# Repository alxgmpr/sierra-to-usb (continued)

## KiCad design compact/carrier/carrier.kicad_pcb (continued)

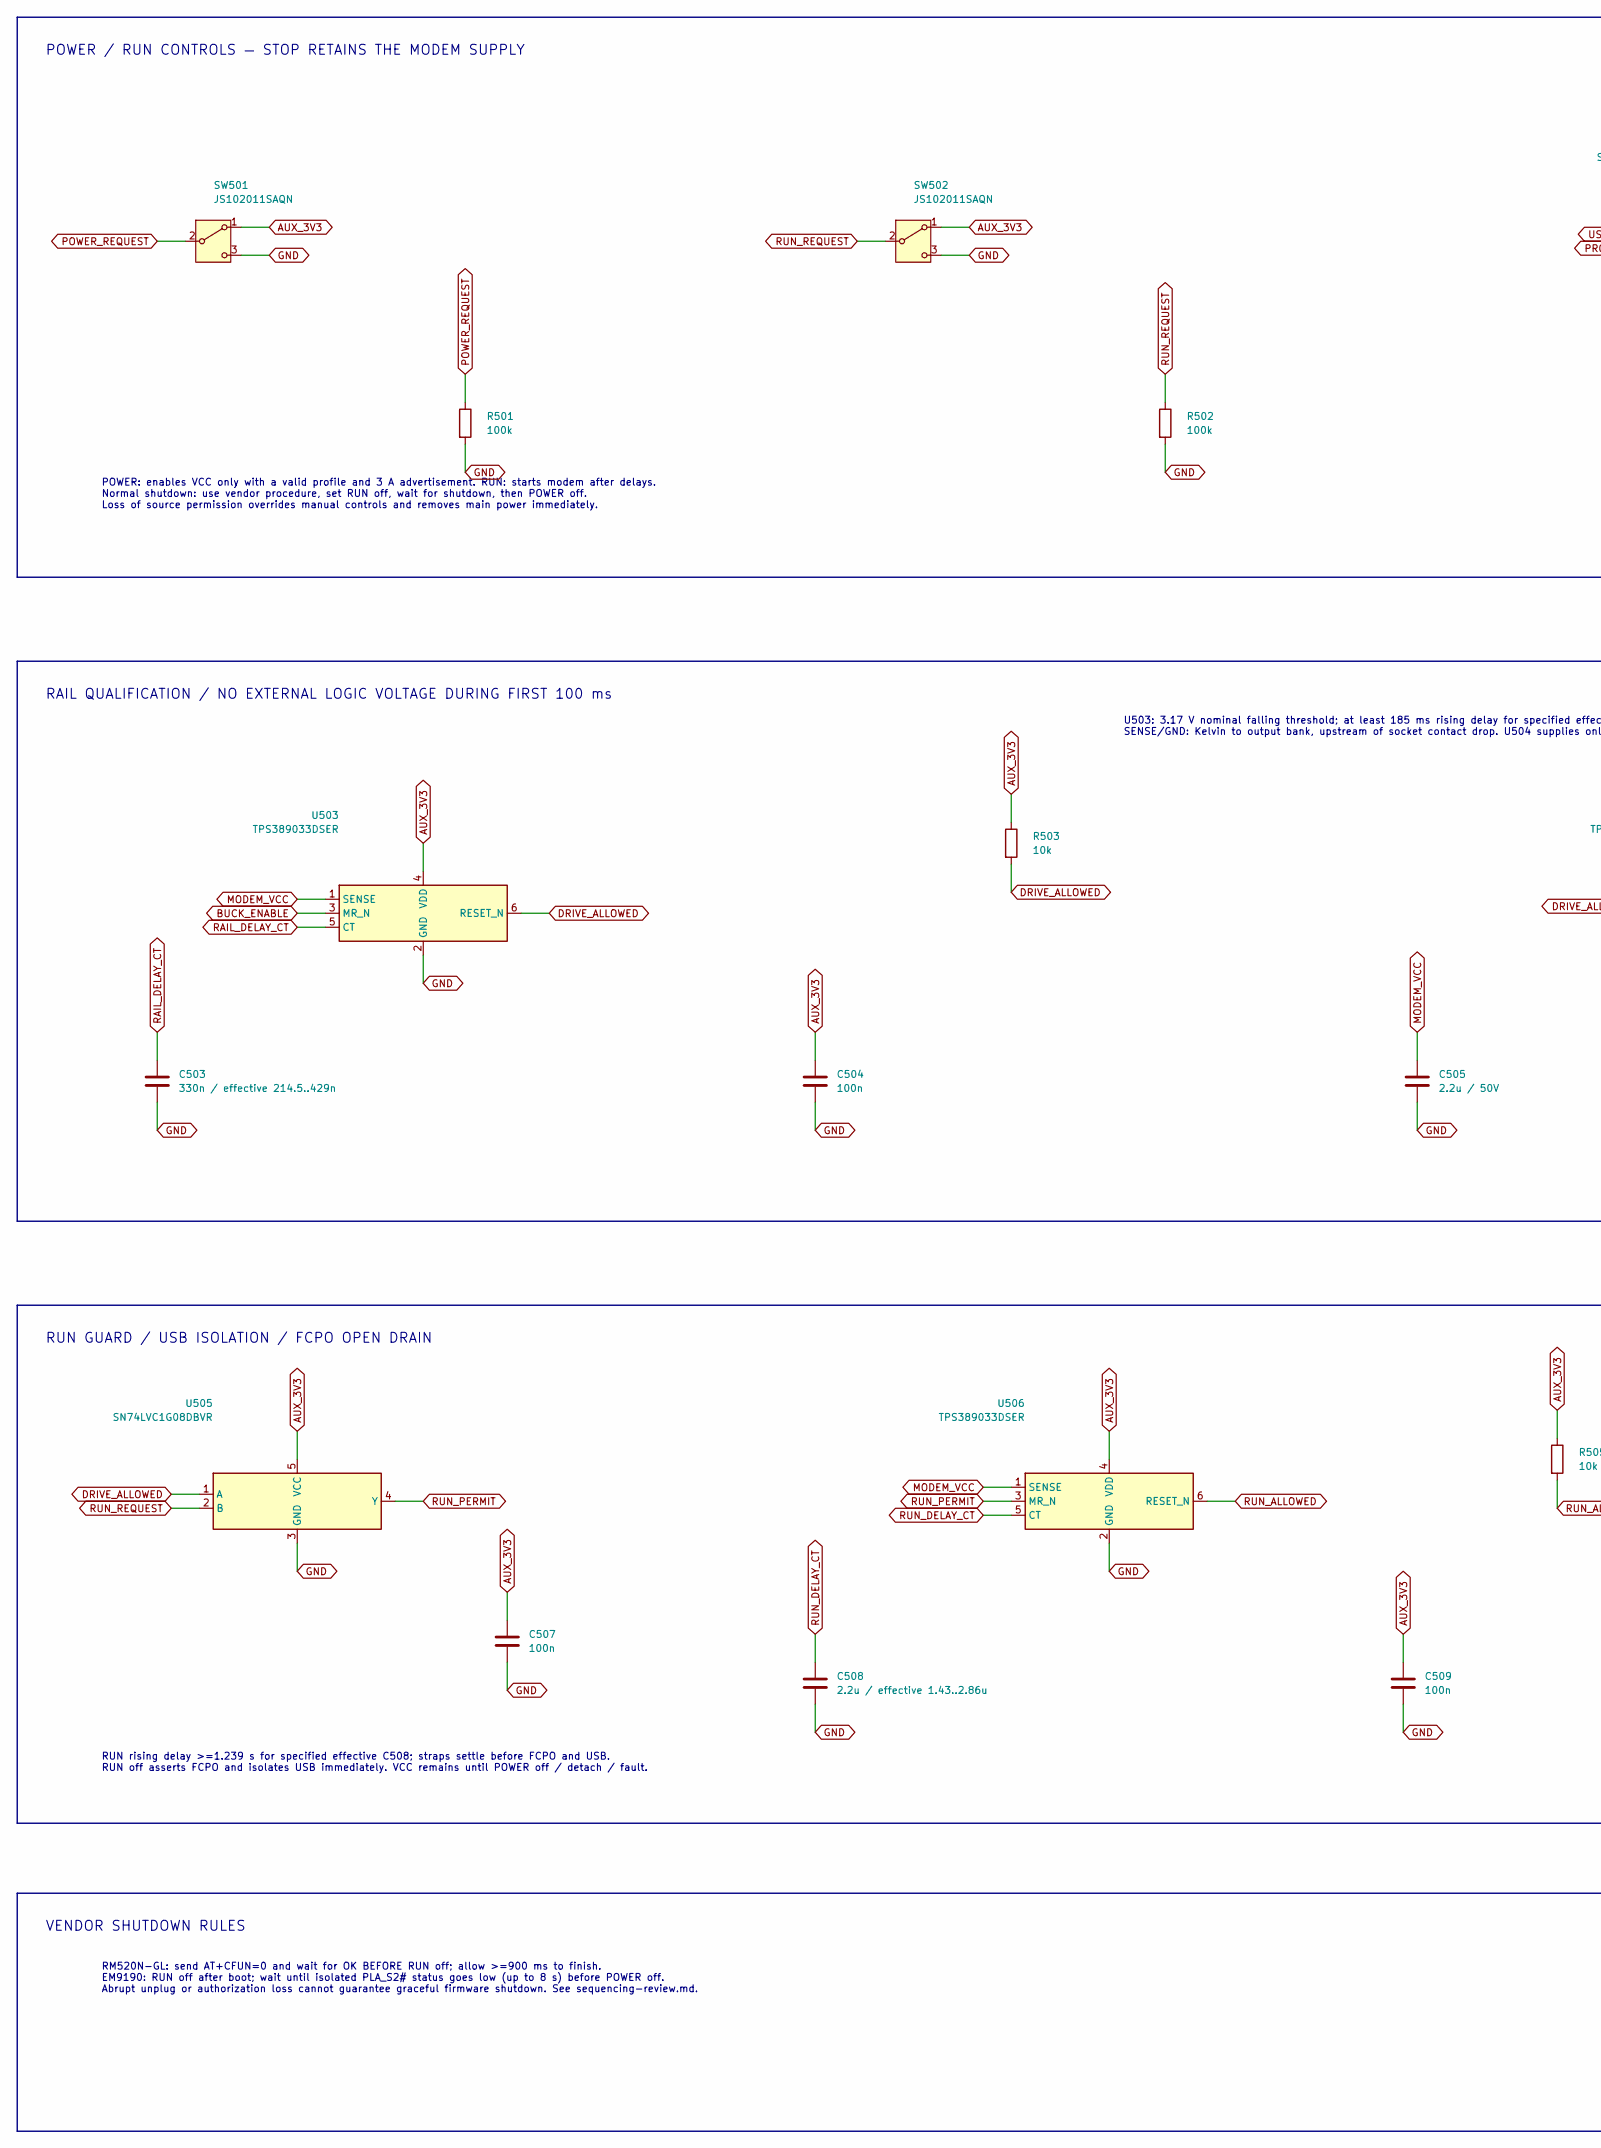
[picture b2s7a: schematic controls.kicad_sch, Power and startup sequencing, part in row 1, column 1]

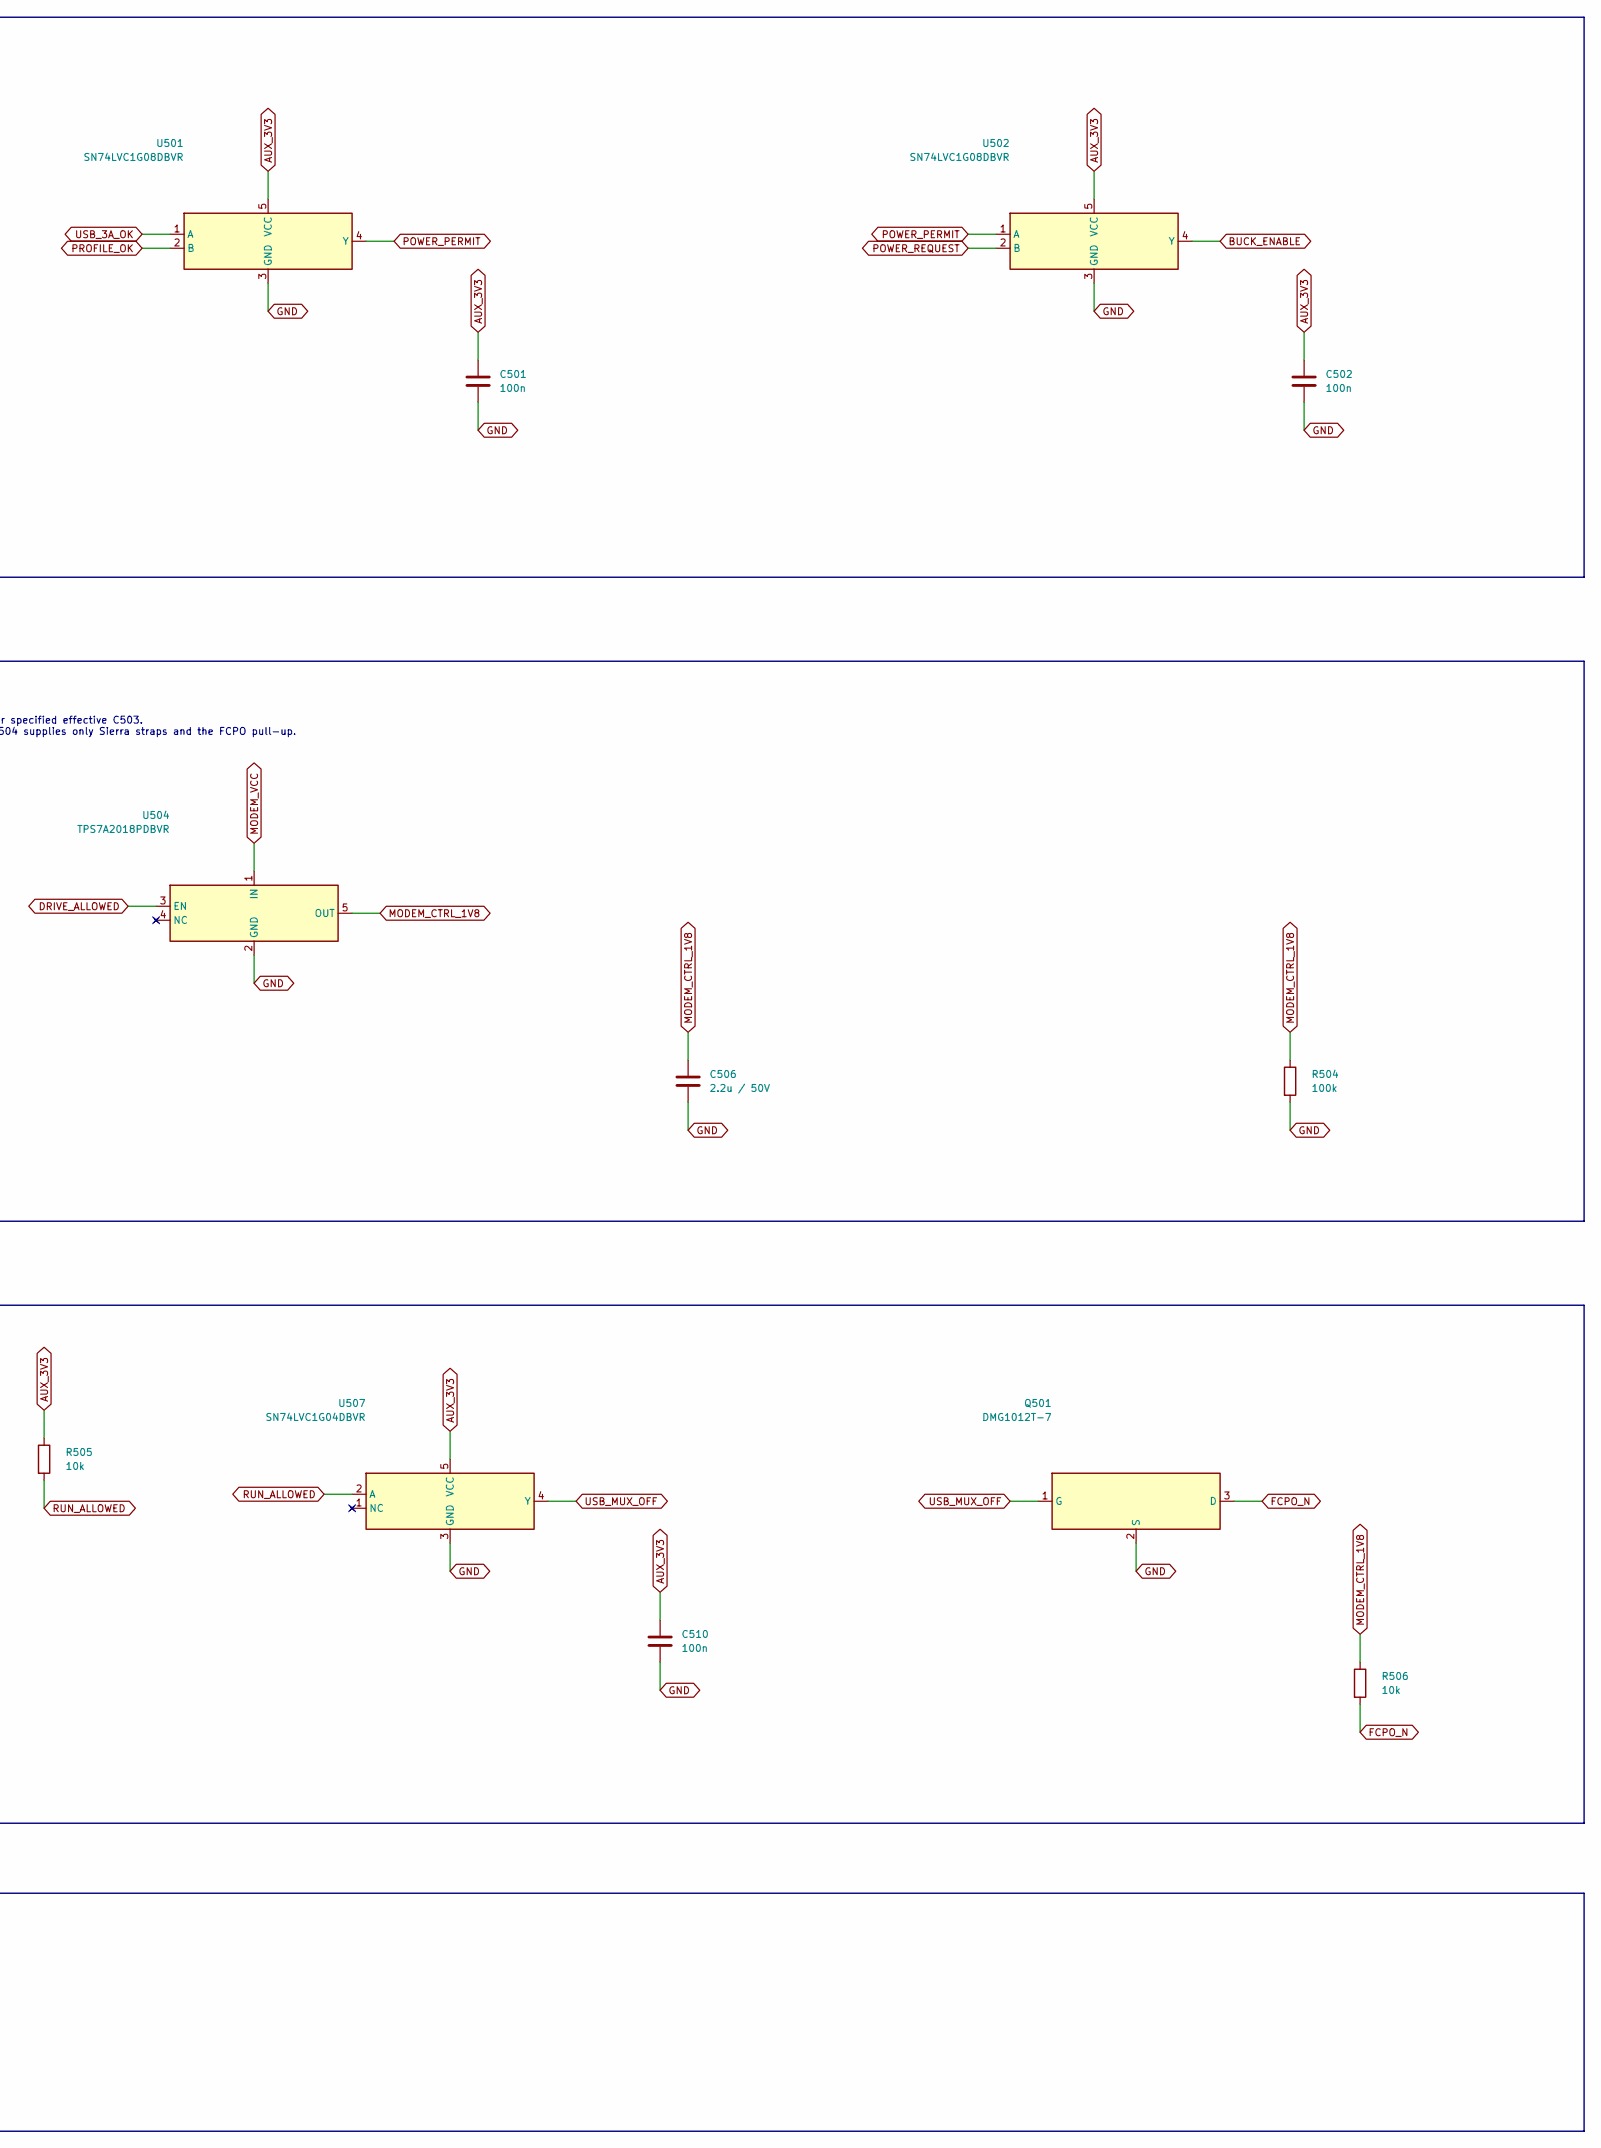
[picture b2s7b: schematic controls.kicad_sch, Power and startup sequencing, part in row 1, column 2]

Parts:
C501, C502, C504, C507, C509, C510: 100n; C_0805_2012Metric; MPN C2012X7R1H104K085AA
C503: 330n / effective 214.5..429n; C_0805_2012Metric; MPN C2012X7R1H334K125AA
C505, C506: 2.2u / 50V; C_1206_3216Metric; MPN C3216X7R1H225K160AB
C508: 2.2u / effective 1.43..2.86u; C_1206_3216Metric; MPN C3216X7R1H225K160AB
Q501: DMG1012T-7; SOT-523; MPN DMG1012T-7
R501, R502, R504: 100k; R_0603_1608Metric; MPN RC0603FR-07100KL
R503, R505, R506: 10k; R_0603_1608Metric; MPN RC0603FR-0710KL
SW501, SW502: JS102011SAQN; SW_SPDT_CK_JS102011SAQN; MPN JS102011SAQN
U501, U502, U505: SN74LVC1G08DBVR; SOT-23-5; MPN SN74LVC1G08DBVR
U503, U506: TPS389033DSER; WSON-6_1.5x1.5mm_P0.5mm; MPN TPS389033DSER
U504: TPS7A2018PDBVR; SOT-23-5; MPN TPS7A2018PDBVR
U507: SN74LVC1G04DBVR; SOT-23-5; MPN SN74LVC1G04DBVR

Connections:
AUX_3V3: C501.1, C502.1, C504.1, C507.1, C509.1, C510.1, R503.1, R505.1, SW501.1 (A), SW502.1 (A), U501.5 (VCC), U502.5 (VCC), U503.4 (VDD), U505.5 (VCC), U506.4 (VDD), U507.5 (VCC); also elsewhere on the board
BUCK_ENABLE: U502.4 (Y), U503.3 (MR_N); also elsewhere on the board
DRIVE_ALLOWED: R503.2, U503.6 (RESET_N), U504.3 (EN), U505.1 (A); also elsewhere on the board
FCPO_N: Q501.3 (D), R506.2; also elsewhere on the board
GND: C501.2, C502.2, C503.2, C504.2, C505.2, C506.2, C507.2, C508.2, C509.2, C510.2, Q501.2 (S), R501.2, R502.2, R504.2, SW501.3 (C), SW502.3 (C), U501.3 (GND), U502.3 (GND), U503.2 (GND), U504.2 (GND), U505.3 (GND), U506.2 (GND), U507.3 (GND); also elsewhere on the board
MODEM_CTRL_1V8: C506.1, R504.1, R506.1, U504.5 (OUT); also elsewhere on the board
MODEM_VCC: C505.1, U503.1 (SENSE), U504.1 (IN), U506.1 (SENSE); also elsewhere on the board
POWER_PERMIT: U501.4 (Y), U502.1 (A)
POWER_REQUEST: R501.1, SW501.2 (B), U502.2 (B)
PROFILE_OK: U501.2 (B); also elsewhere on the board
RAIL_DELAY_CT: C503.1, U503.5 (CT)
RUN_ALLOWED: R505.2, U506.6 (RESET_N), U507.2 (A); also elsewhere on the board
RUN_DELAY_CT: C508.1, U506.5 (CT)
RUN_PERMIT: U505.4 (Y), U506.3 (MR_N)
RUN_REQUEST: R502.1, SW502.2 (B), U505.2 (B)
USB_3A_OK: U501.1 (A); also elsewhere on the board
USB_MUX_OFF: Q501.1 (G), U507.4 (Y); also elsewhere on the board

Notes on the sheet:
POWER / RUN CONTROLS — STOP RETAINS THE MODEM SUPPLY
POWER: enables VCC only with a valid profile and 3 A advertisement. RUN: starts modem after delays. Normal shutdown: use vendor procedure, set RUN off, wait for shutdown, then POWER off. Loss of source permission overrides manual controls and removes main power immediately.
RAIL QUALIFICATION / NO EXTERNAL LOGIC VOLTAGE DURING FIRST 100 ms
U503: 3.17 V nominal falling threshold; at least 185 ms rising delay for specified effective C503. SENSE/GND: Kelvin to output bank, upstream of socket contact drop. U504 supplies only Sierra straps and the FCPO pull-up.
RUN GUARD / USB ISOLATION / FCPO OPEN DRAIN
RUN rising delay >=1.239 s for specified effective C508; straps settle before FCPO and USB. RUN off asserts FCPO and isolates USB immediately. VCC remains until POWER off / detach / fault.
VENDOR SHUTDOWN RULES
RM520N-GL: send AT+CFUN=0 and wait for OK BEFORE RUN off; allow >=900 ms to finish. EM9190: RUN off after boot; wait until isolated PLA_S2# status goes low (up to 8 s) before POWER off. Abrupt unplug or authorization loss cannot guarantee graceful firmware shutdown. See sequencing-review.md.

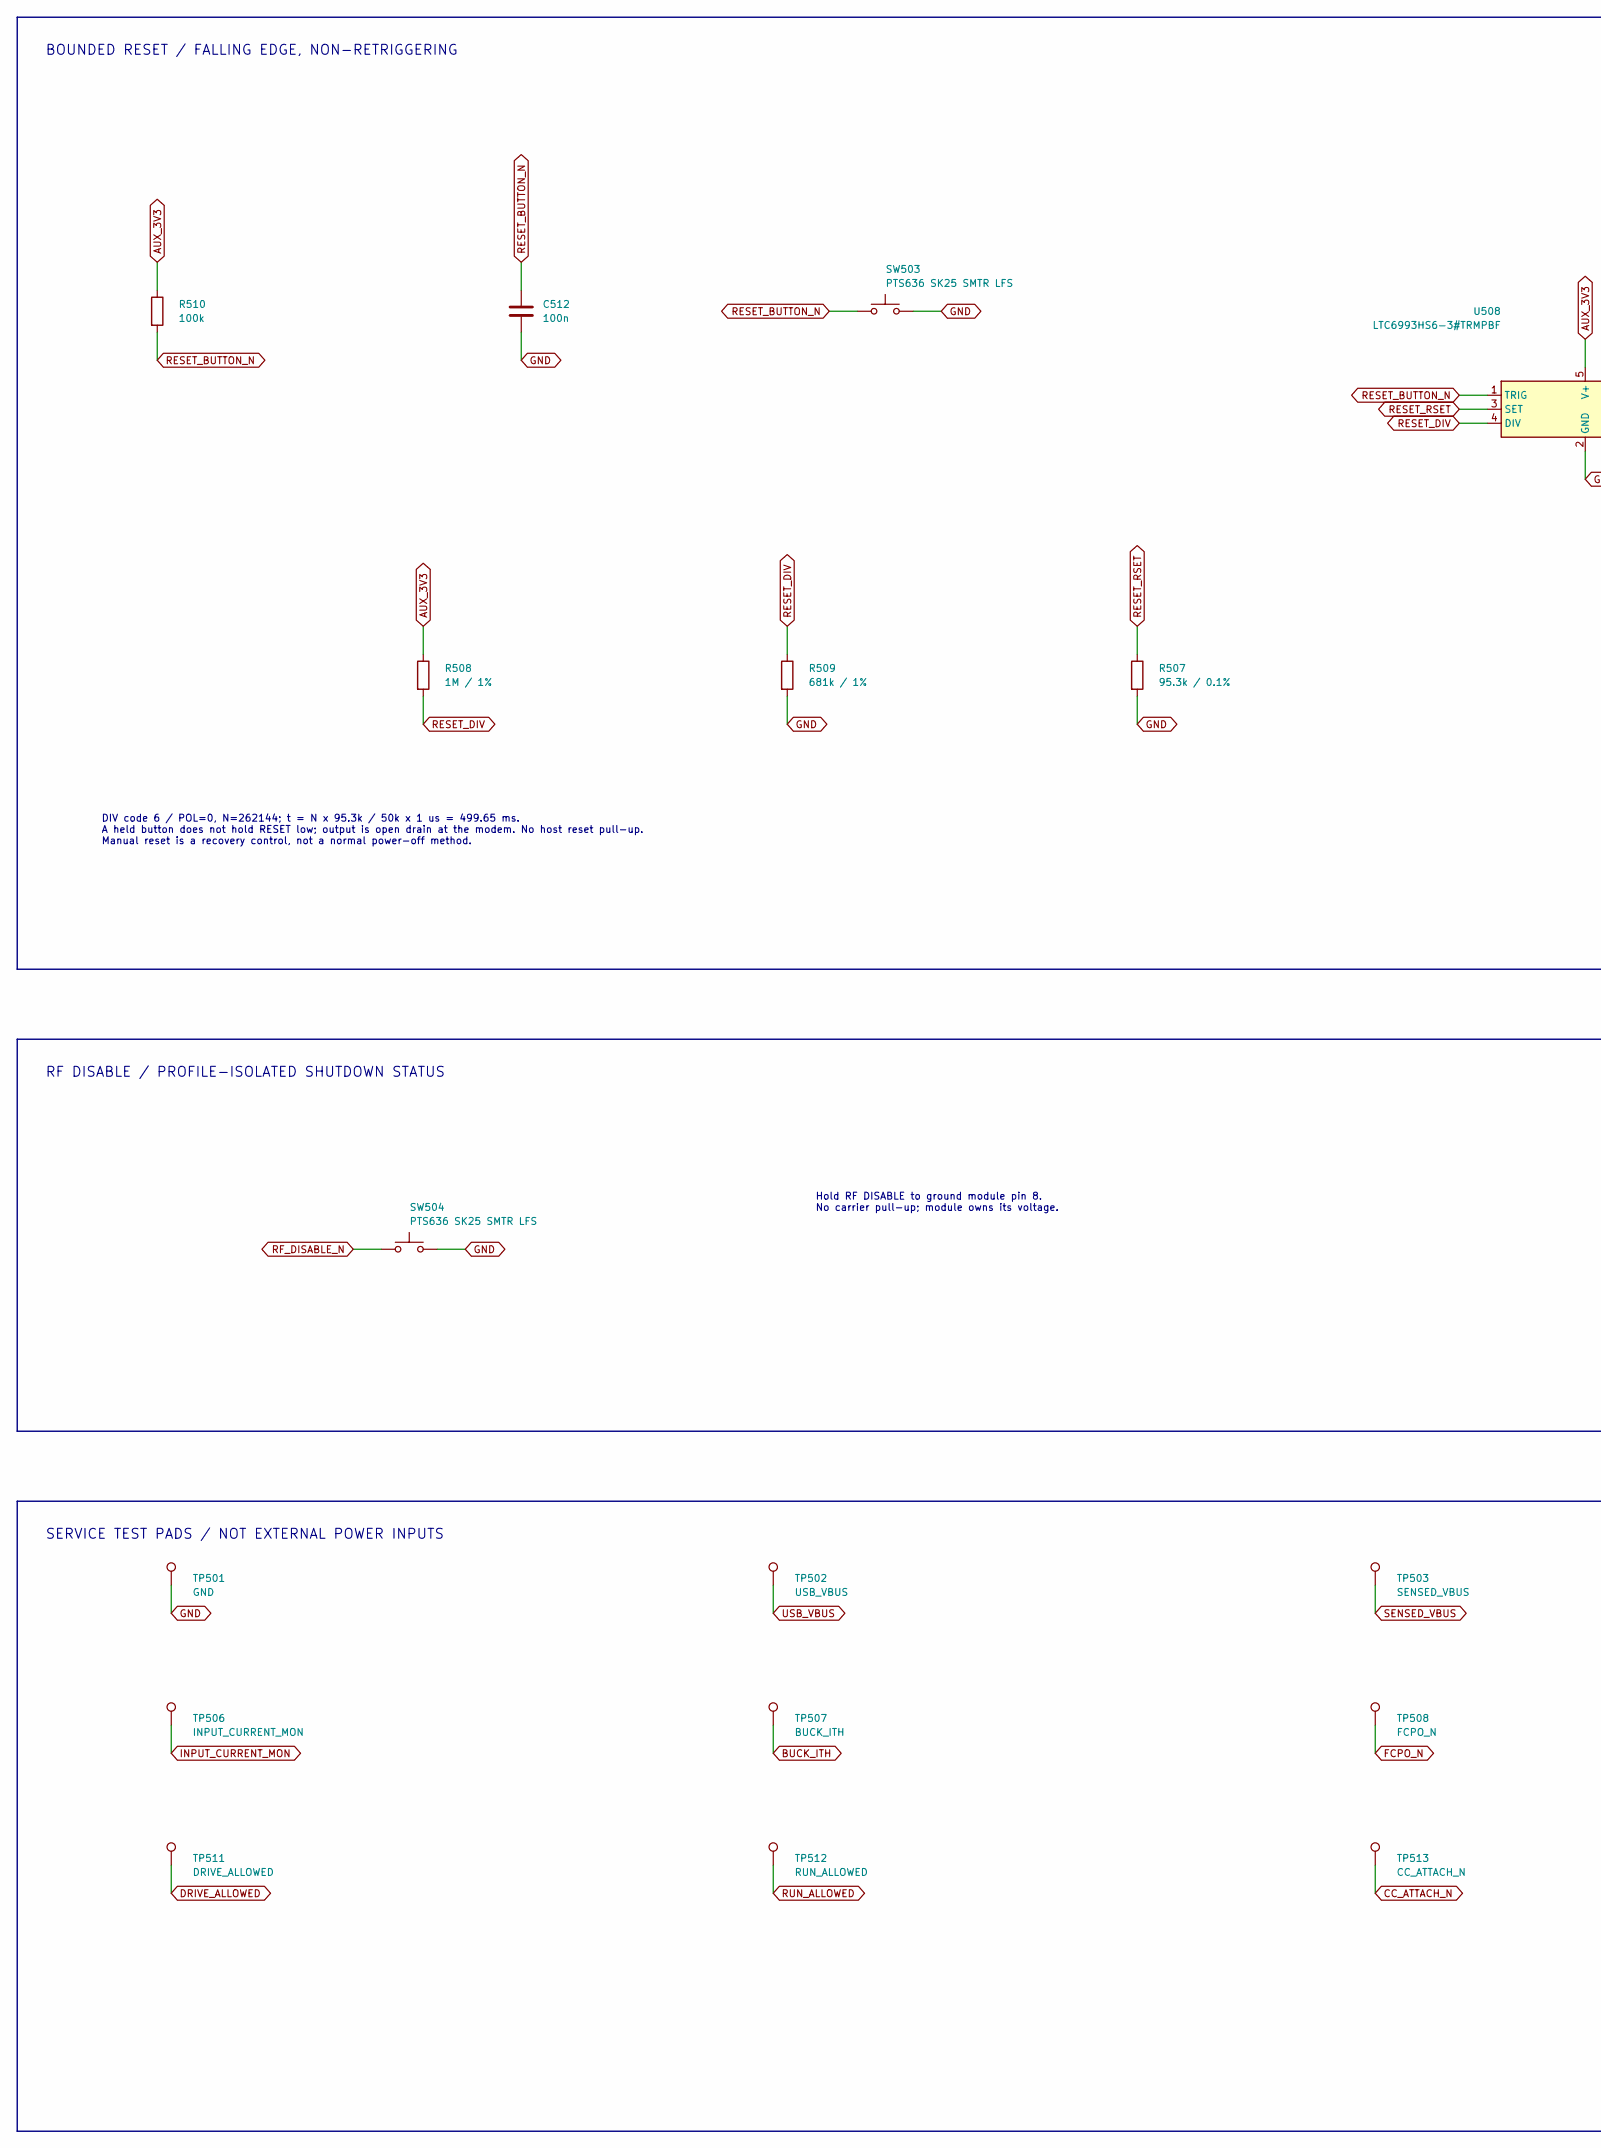
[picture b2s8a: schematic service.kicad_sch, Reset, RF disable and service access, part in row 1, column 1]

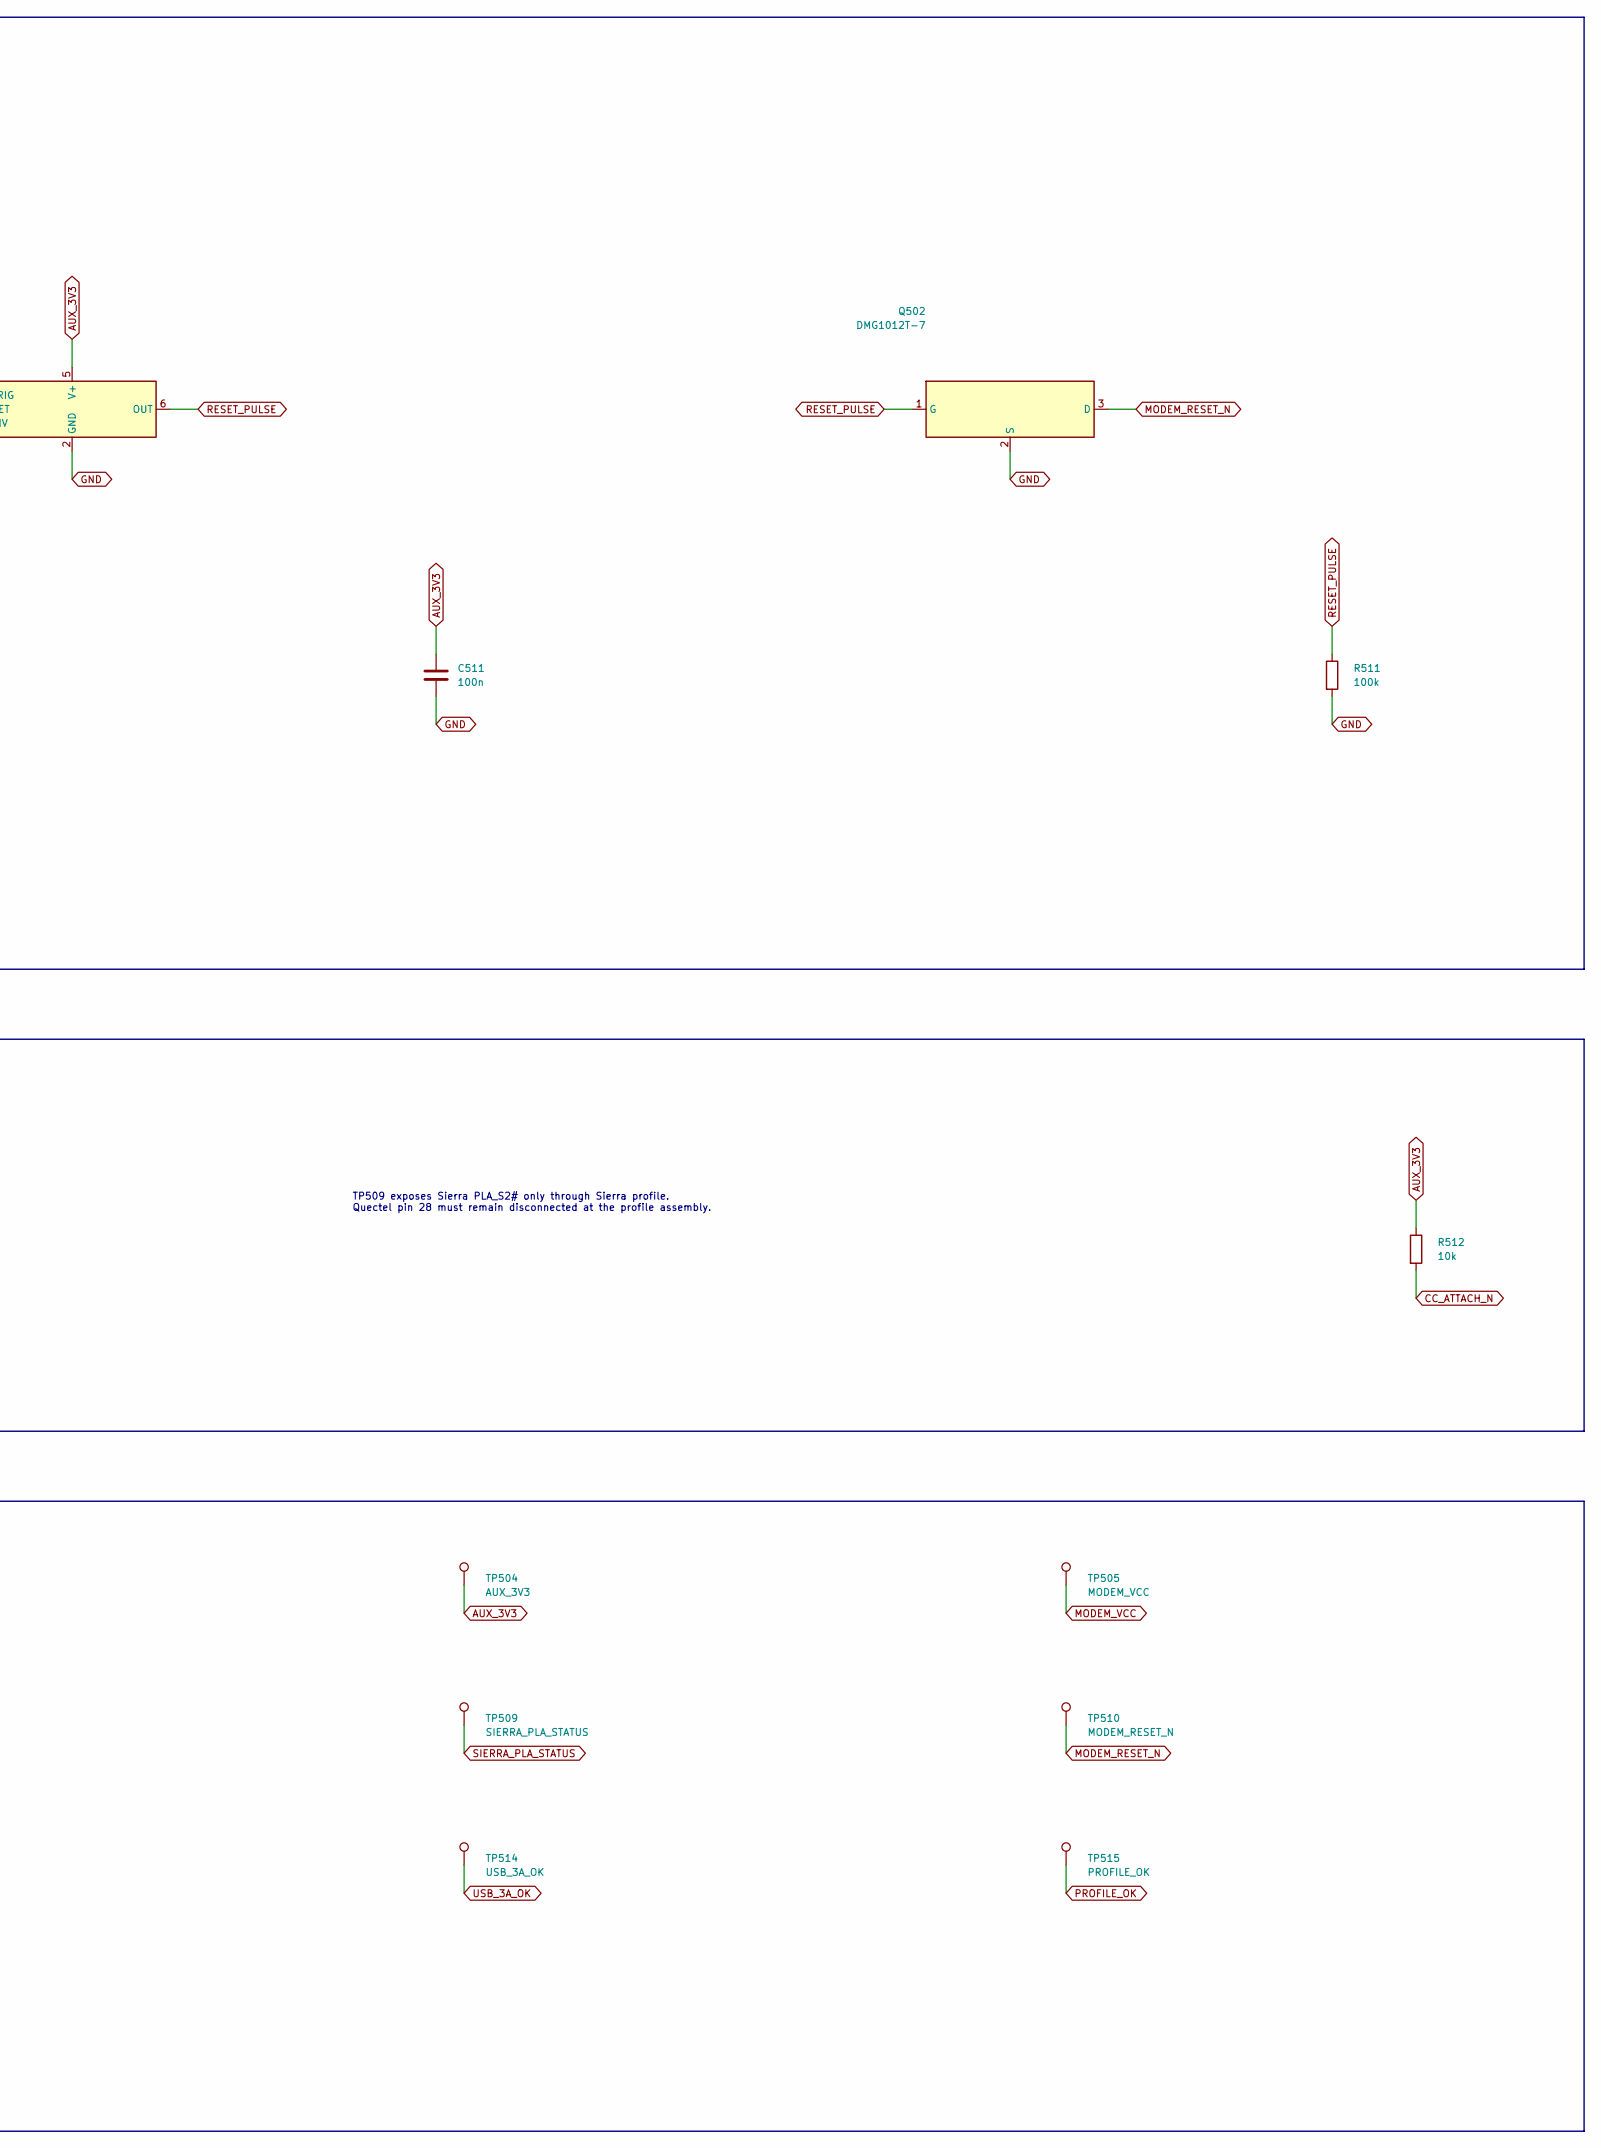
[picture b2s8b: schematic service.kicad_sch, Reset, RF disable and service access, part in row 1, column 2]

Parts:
C511, C512: 100n; C_0805_2012Metric; MPN C2012X7R1H104K085AA
Q502: DMG1012T-7; SOT-523; MPN DMG1012T-7
R507: 95.3k / 0.1%; R_0603_1608Metric; MPN RT0603BRD0795K3L
R508: 1M / 1%; R_0603_1608Metric; MPN RC0603FR-071ML
R509: 681k / 1%; R_0603_1608Metric; MPN RC0603FR-07681KL
R510, R511: 100k; R_0603_1608Metric; MPN RC0603FR-07100KL
R512: 10k; R_0603_1608Metric; MPN RC0603FR-0710KL
SW503, SW504: PTS636 SK25 SMTR LFS; SW_Tactile_SPST_NO_Straight_CK_PTS636Sx25SMTRLFS; MPN PTS636 SK25 SMTR LFS
TP501: GND; TestPoint_Pad_D1.0mm; MPN PCB_TEST_PAD
TP502: USB_VBUS; TestPoint_Pad_D1.0mm; MPN PCB_TEST_PAD
TP503: SENSED_VBUS; TestPoint_Pad_D1.0mm; MPN PCB_TEST_PAD
TP504: AUX_3V3; TestPoint_Pad_D1.0mm; MPN PCB_TEST_PAD
TP505: MODEM_VCC; TestPoint_Pad_D1.0mm; MPN PCB_TEST_PAD
TP506: INPUT_CURRENT_MON; TestPoint_Pad_D1.0mm; MPN PCB_TEST_PAD
TP507: BUCK_ITH; TestPoint_Pad_D1.0mm; MPN PCB_TEST_PAD
TP508: FCPO_N; TestPoint_Pad_D1.0mm; MPN PCB_TEST_PAD
TP509: SIERRA_PLA_STATUS; TestPoint_Pad_D1.0mm; MPN PCB_TEST_PAD
TP510: MODEM_RESET_N; TestPoint_Pad_D1.0mm; MPN PCB_TEST_PAD
TP511: DRIVE_ALLOWED; TestPoint_Pad_D1.0mm; MPN PCB_TEST_PAD
TP512: RUN_ALLOWED; TestPoint_Pad_D1.0mm; MPN PCB_TEST_PAD
TP513: CC_ATTACH_N; TestPoint_Pad_D1.0mm; MPN PCB_TEST_PAD
TP514: USB_3A_OK; TestPoint_Pad_D1.0mm; MPN PCB_TEST_PAD
TP515: PROFILE_OK; TestPoint_Pad_D1.0mm; MPN PCB_TEST_PAD
U508: LTC6993HS6-3#TRMPBF; TSOT-23-6; MPN LTC6993HS6-3#TRMPBF

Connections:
AUX_3V3: C511.1, R508.1, R510.1, R512.1, TP504.1, U508.5 (V+); also elsewhere on the board
BUCK_ITH: TP507.1; also elsewhere on the board
CC_ATTACH_N: R512.2, TP513.1; also elsewhere on the board
DRIVE_ALLOWED: TP511.1; also elsewhere on the board
FCPO_N: TP508.1; also elsewhere on the board
GND: C511.2, C512.2, Q502.2 (S), R507.2, R509.2, R511.2, SW503.2, SW504.2, TP501.1, U508.2 (GND); also elsewhere on the board
INPUT_CURRENT_MON: TP506.1; also elsewhere on the board
MODEM_RESET_N: Q502.3 (D), TP510.1; also elsewhere on the board
MODEM_VCC: TP505.1; also elsewhere on the board
PROFILE_OK: TP515.1; also elsewhere on the board
RESET_BUTTON_N: C512.1, R510.2, SW503.1, U508.1 (TRIG)
RESET_DIV: R508.2, R509.1, U508.4 (DIV)
RESET_PULSE: Q502.1 (G), R511.1, U508.6 (OUT)
RESET_RSET: R507.1, U508.3 (SET)
RF_DISABLE_N: SW504.1; also elsewhere on the board
RUN_ALLOWED: TP512.1; also elsewhere on the board
SENSED_VBUS: TP503.1; also elsewhere on the board
SIERRA_PLA_STATUS: TP509.1; also elsewhere on the board
USB_3A_OK: TP514.1; also elsewhere on the board
USB_VBUS: TP502.1; also elsewhere on the board

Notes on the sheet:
BOUNDED RESET / FALLING EDGE, NON-RETRIGGERING
DIV code 6 / POL=0, N=262144; t = N x 95.3k / 50k x 1 us = 499.65 ms. A held button does not hold RESET low; output is open drain at the modem. No host reset pull-up. Manual reset is a recovery control, not a normal power-off method.
RF DISABLE / PROFILE-ISOLATED SHUTDOWN STATUS
Hold RF DISABLE to ground module pin 8. No carrier pull-up; module owns its voltage.
TP509 exposes Sierra PLA_S2# only through Sierra profile. Quectel pin 28 must remain disconnected at the profile assembly.
SERVICE TEST PADS / NOT EXTERNAL POWER INPUTS

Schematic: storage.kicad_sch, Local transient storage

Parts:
C405, C406, C415, C416: 220u / 6.3V; KEMET_D_7343_Median; MPN T530D227M006ATE005

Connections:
GND: C405.2, C406.2, C415.2, C416.2; also elsewhere on the board
MODEM_VCC: C405.1, C406.1, C415.1, C416.1; also elsewhere on the board

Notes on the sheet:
LOCAL STORAGE / LIVE SOURCE REMAINS CONNECTED
Anode marking faces MODEM_VCC. No series storage switch. The buck supplies the load continuously; these capacitors supply only the temporary difference during a load step.
Bank: 880 uF nominal, 704 uF at -20% initial tolerance. At -20% endurance change: 563.2 uF (before temperature). ESR: 5 mOhm each maximum initially; bank 1.25 mOhm. At 2x endurance ESR: bank 2.5 mOhm (before temperature). These are specified qualification-test limits, not an unlimited lifetime guar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
Local 22 uF ceramics remain on the regulator sheet. Place the polymer bank close to the M.2 VCC distribution, with short, broad supply and return connections. No routing, filled copper or thermal vias are generated.

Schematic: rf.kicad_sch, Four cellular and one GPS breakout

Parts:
J601, J603, J605, J607, J609: 20449-001E-03; IPEX_MHF4_20449_001E_03; MPN 20449-001E-03
J602, J604, J606, J608, J610: 132289; SMA_Amphenol_132289_Manufacturer; MPN 132289

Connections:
GND: J601.2 (Ext), J602.2 (Ext), J603.2 (Ext), J604.2 (Ext), J605.2 (Ext), J606.2 (Ext), J607.2 (Ext), J608.2 (Ext), J609.2 (Ext), J610.2 (Ext); also elsewhere on the board
RF1: J601.1 (In), J602.1 (In)
RF2: J603.1 (In), J604.1 (In)
RF3: J605.1 (In), J606.1 (In)
RF4: J607.1 (In), J608.1 (In)
RF_GPS: J609.1 (In), J610.1 (In)

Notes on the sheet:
FIVE PASSIVE 50 OHM ANTENNA BREAKOUTS
50 ohm PCB launch
RF1..RF4 are neutral port IDs. Connect all four module antennas using four CAB.01072 harnesses. GPS: fifth CAB.01072 only for a dedicated module GNSS port. Sierra mapping: RF1 MAIN / RF2 MIMO1 RF3 MIMO2 / RF4 AUX Quectel mapping: RF1 ANT0 / RF2 ANT1 RF3 ANT2 / RF4 ANT3 No active GNSS bias supply. N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
Coax harnesses terminate at module RF receptacles, not at M.2 edge contacts.

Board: 4 copper layers, 168 parts (0 on the bottom side), 101 nets, no tracks yet.

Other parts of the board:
H1: H1
H2: H2
H3: H3
H4: H4
H5: H5
H10: H10
MECH1: MECH1
